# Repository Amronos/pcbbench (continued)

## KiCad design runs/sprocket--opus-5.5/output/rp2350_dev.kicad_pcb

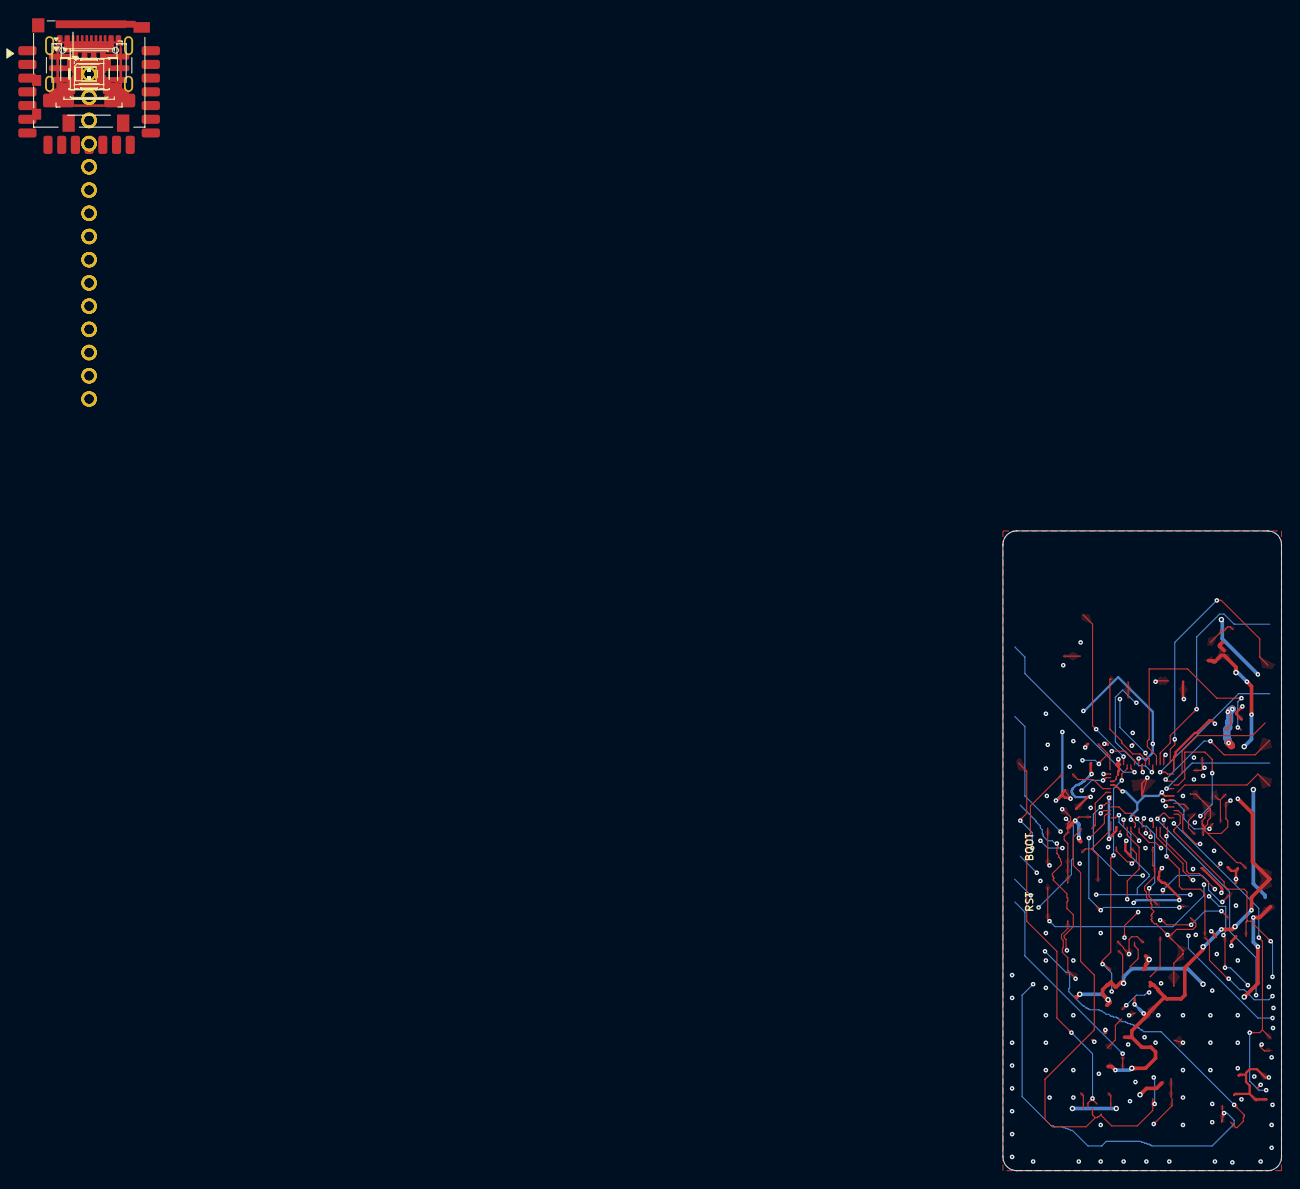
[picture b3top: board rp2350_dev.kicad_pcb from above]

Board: 4 copper layers, 30.5 x 70.0 mm, 82 parts (0 on the bottom side), 66 nets.

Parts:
C1: 4.7 µF; C_0603_1608Metric
C2, C3, C4, C5, C18, C30, C40: 10 µF; C_0603_1608Metric
C6, C7, C10, C11, C12, C13, C14, C15, C16, C17, C19, C20, C21, C27, C28, C31, C32, C41, C42: 100 nF; C_0402_1005Metric
C22, C23, C24, C29: 4.7 µF; C_0402_1005Metric
C25, C26: 15 pF; C_0402_1005Metric
D1: WS2812C-2020-V6; LED_WS2812B-2020_PLCC4_2.0x2.0mm
D2: red; LED_0603_1608Metric
FID1, FID2, FID3: Fiducial; Fiducial_1mm_Mask2mm
J1: USB-C; USB_C_Receptacle_GCT_USB4105-xx-A_16P_TopMnt_Horizontal
J2: microSD; microSD_HC_Molex_104031-0811
J3: Qwiic; JST_SH_SM04B-SRSS-TB_1x04-1MP_P1.00mm_Horizontal
J4: LiPo; JST_PH_S2B-PH-SM4-TB_1x02-1MP_P2.00mm_Horizontal
J5: Header L; PinHeader_1x15_P2.54mm_Vertical
J6: Header R; PinHeader_1x15_P2.54mm_Vertical
L1: 3.3 µH; L_Abracon_AOTA-B201610S
R1, R2: 5.1 kΩ; R_0402_1005Metric
R3, R31, R40, R41, R42, R43, R44, R45: 10 kΩ; R_0402_1005Metric
R4, R24: 2.7 kΩ; R_0402_1005Metric
R5: 1.6 kΩ; R_0402_1005Metric
R6, R21, R25: 1 kΩ; R_0402_1005Metric
R9, R10, R11, R13: 100 kΩ; R_0402_1005Metric
R12: 68 kΩ; R_0402_1005Metric
R20: 33 Ω; R_0402_1005Metric
R22, R23: 27 Ω; R_0402_1005Metric
R30: 470 Ω; R_0402_1005Metric
R46, R47: 4.7 kΩ; R_0402_1005Metric
SW1: BOOTSEL; SW_SPST_PTS810
SW2: RESET; SW_SPST_PTS810
U1: RP2350A; QFN-60-1EP_7x7mm_P0.4mm_EP3.4x3.4mm
U2: W25Q128JVSIQ; SOIC-8_5.3x5.3mm_P1.27mm
U3: APS6404L-3SQR-SN; SOIC-8_3.9x4.9mm_P1.27mm
U4: RMC20452T
U5: BQ24074RGTR; VQFN-16-1EP_3x3mm_P0.5mm_EP1.68x1.68mm_ThermalVias
U6: TLV75733PDBVR; SOT-23-5
U7: USBLC6-2SC6; SOT-23-6
Y1: 12 MHz; Crystal_SMD_3225-4Pin_3.2x2.5mm

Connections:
3V3_EN: J5.14, R9.2, U6.3 (EN)
+1V1: C19.1, C20.1, C21.1, C23.1, C29.1, L1.2, U1.6 (DVDD), U1.23 (DVDD), U1.39 (DVDD), U1.50 (VREG_FB)
+3V3: C5.1, C6.1, C10.1, C11.1, C12.1, C13.1, C14.1, C15.1, C16.1, C17.1, C18.1, C22.1, C27.1, C28.1, C32.1, C40.1, C41.1, C42.1, D1.4 (VDD), J2.4 (VDD), J3.2, J5.4, J6.11, R20.1, R24.1, R40.1, R41.1, R42.1, R43.1, R44.1, R45.1, R46.1, R47.1, U1.1 (IOVDD), U1.11 (IOVDD), U1.20 (IOVDD), U1.30 (IOVDD), U1.38 (IOVDD), U1.44 (ADC_AVDD), U1.45 (IOVDD), U1.49 (VREG_VIN), U1.53 (USB_OTP_VDD), U1.54 (QSPI_IOVDD), U2.8 (VCC), U3.8 (VDD), U4.14 (VDDIO), U6.5 (OUT)
/mcu/BOOT_SW: R25.2, SW1.1
/mcu/PSRAM_CS: R24.2, U1.12 (GPIO8), U3.1 (~CE)
/mcu/QSPI_SCLK: U1.56 (QSPI_SCLK), U2.6 (CLK), U3.6 (SCLK)
/mcu/QSPI_SD0: U1.57 (QSPI_SD0), U2.5 (DI/IO_{0}), U3.5 (SI/SIO0)
/mcu/QSPI_SD1: U1.59 (QSPI_SD1), U2.2 (DO/IO_{1}), U3.2 (SO/SIO1)
/mcu/QSPI_SD2: U1.58 (QSPI_SD2), U2.3 (~WP/IO_{2}), U3.3 (SIO2)
/mcu/QSPI_SD3: U1.55 (QSPI_SD3), U2.7 (~HOLD/~RESET/IO_{3}), U3.7 (SIO3)
/mcu/QSPI_SS: R25.1, U1.60 (~QSPI_SS), U2.1 (~CS)
/mcu/USB_DM_MCU: R23.2, U1.51 (USB_DM)
/mcu/USB_DP_MCU: R22.2, U1.52 (USB_DP)
/mcu/VREG_AVDD: C24.1, R20.2, U1.46 (VREG_AVDD)
/mcu/VREG_LX: L1.1, U1.48 (VREG_LX)
/mcu/XIN: C25.1, U1.21 (XIN), Y1.1
/mcu/XOUT: R21.2, U1.22 (XOUT)
/mcu/XTAL_O: C26.1, R21.1, Y1.3
/power/BQ_ILIM: R5.1, U5.12 (ILIM)
/power/BQ_ISET: R4.1, U5.16 (ISET)
/power/BQ_TS: R3.1, U5.1 (TS)
/power/CC1: J1.A5 (CC1), R1.1
/power/CC2: J1.B5 (CC2), R2.1
/power/CHG_LED_K: D2.1 (K), R6.1
/power/CHG_N: R6.2, U5.9 (~CHG)
/wireless/WL_DOUT: R30.2, U4.6 (WL_DATA_OUT)
/wireless/WL_IRQ: R31.2, U4.10 (~WL_IRQ)
GND: C1.2, C2.2, C3.2, C4.2, C5.2, C6.2, C7.2, C10.2, C11.2, C12.2, C13.2, C14.2, C15.2, C16.2, C17.2, C18.2, C19.2, C20.2, C21.2, C22.2, C23.2, C24.2, C25.2, C26.2, C27.2, C28.2, C29.2, C30.2, C31.2, C32.2, C40.2, C41.2, C42.2, D1.2 (VSS), J1.A1 (GND), J1.A12 (GND), J1.B1 (GND), J1.B12 (GND), J1.SH (SHIELD), J2.6 (VSS), J2.10 (DET_A), J2.SH (SHIELD), J3.1, J4.1, J5.1, J5.5, J5.15, J6.1, J6.15, R1.2, R2.2, R3.2, R4.2, R5.2, R11.2, R13.2, SW1.2, SW2.2, U1.47 (VREG_PGND), U1.61 (GND), U2.4 (GND), U3.4 (VSS), U4.1 (GND), U4.4 (GND), U4.7 (GND), U4.11 (GND), U4.15 (GND), U4.21 (GND), U5.4 (~CE), U5.5 (EN2), U5.8 (VSS), U5.17 (VSS), U6.2 (GND), U7.2 (GND), Y1.2 (G), Y1.4 (G)
GPIO0: J5.6, U1.2 (GPIO0)
GPIO1: J5.7, U1.3 (GPIO1)
GPIO2: J5.8, U1.4 (GPIO2)
GPIO3: J5.9, U1.5 (GPIO3)
GPIO6: J5.12, U1.9 (GPIO6)
GPIO7: J5.13, U1.10 (GPIO7)
GPIO16: J6.7, U1.27 (GPIO16)
GPIO17: J6.6, U1.28 (GPIO17)
GPIO18: J6.5, U1.29 (GPIO18)
GPIO19: J6.4, U1.31 (GPIO19)
GPIO20: J6.3, U1.32 (GPIO20)
GPIO21: J6.2, U1.33 (GPIO21)
GPIO26: J5.2, U1.40 (GPIO26/ADC0)
GPIO27: J5.3, U1.41 (GPIO27/ADC1)
I2C_SCL: J3.4, J5.11, R47.2, U1.8 (GPIO5)
I2C_SDA: J3.3, J5.10, R46.2, U1.7 (GPIO4)
LED_DIN: D1.3 (DIN), U1.34 (GPIO22)
RUN: J6.10, SW2.1, U1.26 (RUN)
SD_CLK: J2.5 (CLK), U1.14 (GPIO10)
SD_CMD: J2.3 (CMD), R42.2, U1.15 (GPIO11)
SD_D0: J2.7 (DAT0), R43.2, U1.16 (GPIO12)
SD_D1: J2.8 (DAT1), R44.2, U1.17 (GPIO13)
SD_D2: J2.1 (DAT2), R40.2, U1.18 (GPIO14)
SD_D3: J2.2 (DAT3/CD), R41.2, U1.19 (GPIO15)
SD_DET: J2.9 (DET_B), R45.2, U1.13 (GPIO9)
SWCLK: J6.9, U1.24 (SWCLK)
SWDIO: J6.8, U1.25 (SWDIO)
USB_DM: J1.A7 (D-), J1.B7 (D-), R23.1, U7.3 (I/O2), U7.4 (I/O2)
USB_DP: J1.A6 (D+), J1.B6 (D+), R22.1, U7.1 (I/O1), U7.6 (I/O1)
VBAT: C3.1, J4.2, J6.12, R10.1, U5.2 (BAT), U5.3 (BAT)
VBAT_SENSE: C7.1, R10.2, R11.1, U1.42 (GPIO28/ADC2)
VBUS: C1.1, D2.2 (A), J1.A4 (VBUS), J1.A9 (VBUS), J1.B4 (VBUS), J1.B9 (VBUS), J6.14, R12.1, U5.13 (IN), U7.5 (VBUS)
VBUS_SENSE: R12.2, R13.1, U4.17 (WL_GPIO2)
VSYS: C2.1, C4.1, C30.1, C31.1, J6.13, R9.1, U4.16 (VIN), U5.6 (EN1), U5.10 (OUT), U5.11 (OUT), U6.1 (IN)
WL_CLK: U1.43 (GPIO29/ADC3), U4.3 (WL_CLK)
WL_CS: U1.37 (GPIO25), U4.9 (WL_CS)
WL_D: R30.1, R31.1, U1.36 (GPIO24), U4.5 (WL_DATA_IN)
WL_ON: U1.35 (GPIO23), U4.12 (WL_ON), U4.13 (BT_ON)

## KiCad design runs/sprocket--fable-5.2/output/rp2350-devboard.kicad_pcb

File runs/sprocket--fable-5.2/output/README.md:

# RP2350 Wi-Fi dev board

A 76.2 × 25.4 mm, 4-layer RP2350A board laid out for PCBWay turnkey assembly. All assembled parts sit on the top side. The two 1×12 headers are fitted on the bottom, 22.86 mm (0.9 in) apart, so the board plugs into a breadboard with one free hole per side.

| Block | Part | Notes |
|---|---|---|
| MCU | RP2350A (SC1509-A4), QFN-60 | Order the A4 stepping. Core regulator copies Raspberry Pi's reference layout. |
| Flash | W25Q128JVPIQ, 16 MB, WSON-8 | QSPI CS0. IQ variant has QE fixed to 1. |
| PSRAM | APS6404L-3SQR-SN, 8 MB, SOP-8 | QSPI CS1 on GPIO8, 2.2 kΩ pull-up R19 |
| Crystal | ABM8-272-T3 12 MHz | 15 pF load caps, 1 kΩ series on XOUT, as on Pico 2 |
| USB | GCT USB4105-GF-A USB-C, USBLC6-2SC6 ESD, 27 Ω series | USB 2.0 full speed. 5.1 kΩ Rd on each CC pin. |
| Charger | BQ24074RGTR with power path | USB500 mode: 500 mA input limit, 494 mA charge (R6 1.8 kΩ), 10 kΩ TS resistor in place of a thermistor |
| 3.3 V | TLV75733PDBVR LDO, 1 A | Input is VSYS. EN is pulled up to VSYS and brought out to J7. |
| Battery | JST PH 2-pin (S2B-PH-SM4-TB) | Pin 1 is +, marked on silkscreen. VBAT/2 on GPIO28 (ADC2). |
| Radio | Raspberry Pi RM2 (CYW43439), Wi-Fi 4 + BLE 5.2 | Same GPIO23/24/25/29 wiring as Pico 2 W |
| microSD | Hirose DM3AT-SF-PEJM5 | GPIO10 to GPIO15, usable as SPI1 or 4-bit SDIO via PIO. 10 kΩ pull-ups, 10 µF local bulk. |
| Qwiic | JST SH 4-pin | I2C0 on GPIO4/GPIO5, 2.2 kΩ pull-ups |
| Debug | JST SH 3-pin | Raspberry Pi debug connector pinout, 100 Ω series |
| RGB LED | WS2812B-2020-V6 on GPIO9 | V6 is the variant rated for 3.3 V supply |
| LEDs | Green = power good, amber = charging, green = user LED on RM2 WL_GPIO0 | |
| Buttons | BOOT (QSPI_SS via 1 kΩ), RST (RUN) | |

## Pinout

Viewed from the top with the USB-C connector on the left, J6 is the top edge and J7 the bottom edge. Pin 1 of each header is next to the USB end. The same labels are printed on the bottom silkscreen.

| Pin | J6 (top edge) | J7 (bottom edge) |
|---|---|---|
| 1 | VBUS (5 V, straight from USB-C) | 3V3 |
| 2 | VSYS (charger output, 3.5 to 4.4 V) | EN (LDO enable, pull low to turn 3V3 off) |
| 3 | GND | RUN (low = reset) |
| 4 | GP27 / A1 | GND |
| 5 | GP26 / A0 | GP0 |
| 6 | GP22 | GP1 |
| 7 | GP21 | GP2 |
| 8 | GP20 | GP3 |
| 9 | GP19 | GP4 / SDA (shared with Qwiic) |
| 10 | GP18 | GP5 / SCL (shared with Qwiic) |
| 11 | GP17 | GP6 |
| 12 | GP16 | GP7 |

Internal GPIOs:

| GPIO | Use |
|---|---|
| 8 | PSRAM chip select (XIP_CS1n) |
| 9 | WS2812B data |
| 10 / 11 | microSD CLK / CMD |
| 12 to 15 | microSD DAT0 to DAT3 (DAT3 is CS in SPI mode) |
| 23 / 24 / 25 / 29 | RM2 WL_ON / data / CS / clock, as on Pico 2 W |
| 28 | Battery voltage / 2 (ADC2) |

## Firmware notes

- Start from pico-sdk's `pico2_w` board file and change `PICO_FLASH_SIZE_BYTES` to 16 MB. Remove its VSYS sense on GPIO29 and VBUS sense on WL_GPIO2. RM2 GPIO1 and GPIO2 are not connected here.
- Battery voltage is `2 × ADC2`. Call `adc_gpio_init(28)` so the digital input is off.
- Disable the GPIO8 pad pull-down before enabling XIP_CS1 for the PSRAM.
- The microSD card-detect switch is not connected. Firmware has to probe for a card.
- There is no GPIO for USB presence or charger status. The LEDs show PGOOD and CHG only.

## Layout decisions

- Stackup is PCBWay's standard 4-layer 1.6 mm with 1 oz copper on all layers: F.Cu signals with GND fill, In1 solid GND, In2 3V3 plane with a few signal tracks, B.Cu signals with GND fill. The stackup is written into the board file (7628 prepreg 0.1855 mm, core 1.03 mm, ENIG).
- Rules follow the strictest values in [`scratch/pcbway-notes.md`](scratch/pcbway-notes.md): 0.127 mm (5 mil) track and gap, 0.25 mm drill / 0.55 mm via, 0.15 mm annular ring, 0.5 mm hole to hole, 0.3 mm copper to edge. Two local exceptions are in `rp2350-devboard.kicad_dru`: 0.13 mm around VREG_LX, where the reference layout runs it between 0402 pads, and the USB4105's own peg-to-pad spacing.
- The core regulator (L1, C6, C7, C8) copies Raspberry Pi's reference layout, as the RP2350 datasheet requires. The QSPI bus, U1 fan-out and USB pair were routed by script and locked. An autorouter finished the rest.
- The USB pair is 0.22 mm / 0.15 mm gap over the In1 ground plane. It is not impedance controlled, which full speed USB does not need.
- Power tracks: VBUS and VSYS 0.5 mm, +BATT and 3V3 0.3 mm. 3V3 also uses the In2 plane.
- 40 GND return vias next to signal layer changes, 21 GND stitching vias, and teardrops on all pads and vias.
- The last 5 mm under the RM2 antenna is a keep-out with no copper on any layer. Keep metal away from that end in an enclosure.
- Three fiducials are on the top side. There are no mounting holes: the board is held by its headers.

## Caveats

These come from the design reviews in `scratch/review-*.md` and were accepted, not fixed:

- 3V3 back-feed: anything that powers J7.1 or the Qwiic 3V3 pin while the board is off drives the LDO output above its input. Do not feed 3V3 from outside.
- VBUS on J6.1 is tied straight to USB-C. 5 V fed there back-feeds a connected host. It is not 28 V tolerant, because U6 breaks down at 6 V.
- Battery drain: the 100 kΩ / 100 kΩ divider draws about 21 µA from the cell all the time. With 3V3 off it also feeds GPIO28 through 100 kΩ, which is current-limited and was judged safe.
- No battery protection on the board. Use a cell with its own protection circuit, 500 mAh or larger so 494 mA stays under 1C. Check polarity of third-party cells: many have red and black swapped.
- Without a battery the 500 mA USB limit covers RP2350, Wi-Fi transmit, SD writes and the RGB LED. Heavy peaks can brown out the 3V3 rail. A battery supplements the input.
- On battery, 3V3 drops out of regulation below about 3.5 V. Firmware should stop Wi-Fi and SD writes near 3.4 V.
- GP26 to GP29 are not 5 V tolerant. The other header GPIOs tolerate 5 V only while 3V3 is on.
- No ESD protection on Qwiic, debug or microSD lines.

### Not verified

- DM3AT card-detect pin numbering against the Hirose drawing. The pins are unused, so a mismatch only matters for a later revision.
- PTS810 pad pairing. The KiCad footprint assumes pads 1 and 2 are the switched pair.
- L1 orientation: the AOTA inductor is polarised, and the dot must go to pad 1 (+1V1). This was checked against the footprint, not a physical part.
- No board has been built or measured. All checks are ERC, DRC and datasheet reviews.

## Library notes

- `lib_footprint_mismatch` is set to ignore in the project. J5, J6, J7 and U7 differ from their library copies on purpose: their silkscreen was trimmed where it crossed the board edge.
- KiCad has no 3D models for J2 and D1. Their STEP files in `lib/3d/` came from LCSC through easyeda2kicad (C295747 and C965555, the same 2020 package as the V6 part). The J2 model offset of (1, -3, 0) mm was fitted by eye from renders. These models only affect the renders.
- RM2 symbol and footprint live in `lib/` and match Raspberry Pi's own KiCad footprint.

## Ordering from PCBWay

Upload `fab/rp2350-devboard-gerbers.zip`, `fab/bom-pcbway.csv` and `fab/centroid-top.csv`.

| Setting | Value |
|---|---|
| Layers | 4, order F.Cu / In1.Cu / In2.Cu / B.Cu |
| Thickness | 1.6 mm, standard stackup |
| Min track / spacing | 5/5 mil |
| Min hole | 0.25 mm |
| Copper | 1 oz outer, 1 oz inner |
| Solder mask / silkscreen | Green / white |
| Surface finish | ENIG |
| Panel | Panel by supplier with break-away rails on the long edges. The board is under 50 mm wide and USB-C is at the edge. |
| Assembly | Turnkey, top side only. J6 and J7 are through-hole on the bottom, see BOM notes. |
| Substitutes | No, except lines marked "Yes" in the BOM's substitutes column |
| X-ray | Ask for it on U1 (QFN-60) and U7 (RM2, LGA pads). The price is not in the instant quote. |

Text for the order notes field:

> Machine placement and reflow please, no hand soldering of U1. J1 shell legs are plated through-hole: pin-in-paste or hand solder. J6 and J7 are 1x12 headers fitted on the bottom side, pins pointing down, soldered from the top. L1 is polarised: dot to pad 1, marked on silkscreen. Please quote X-ray for U1 and U7.

Questions for the sales rep are listed at the end of `scratch/pcbway-notes.md`.

## Files

| Path | Content |
|---|---|
| `rp2350-devboard.kicad_pro` / `.kicad_sch` / `.kicad_pcb` | KiCad project |
| `lib/` | RM2 symbol and footprint, J2 and D1 STEP models |
| `docs/schematic.pdf`, `docs/rp2350-devboard.png` | Schematic exports |
| `fab/gerbers/` | 11 Gerber layers, PTH and NPTH drill files, drill maps, Gerber job file |
| `fab/rp2350-devboard-gerbers.zip` | The same files zipped for upload |
| `fab/bom-pcbway.csv` | PCBWay BOM with MPN, LCSC, Digi-Key and Mouser numbers, notes and substitutes |
| `fab/centroid-top.csv` | Pick and place, mm from the bottom-left corner (drill origin) |
| `fab/assembly-top.pdf`, `fab/assembly-bottom.pdf` | Assembly drawings |
| `fab/render-*.png` | 3D renders |
| `scratch/pcbway-notes.md` | PCBWay capabilities with sources, used to set the rules |
| `scratch/review-*.md`, `scratch/jst-polarity.md` | Design reviews |
| `scratch/sch/`, `scratch/pcb/`, `scratch/route/` | Scripts that generate the schematic, place, route and export the board |

### Regenerating

1. `bash scratch/sch/gen_real.sh` rebuilds the schematic, runs ERC and writes the netlist.
2. `scratch/pcb/02_place.py` places parts from `place.json`. `05_fanout.py` draws the hand-routed blocks and the U1 fan-out.
3. `IN2COST=6 bash scratch/route/full.sh g` routes the rest. Copy `g_best.kicad_pcb` to the root.
4. Run `06_unused_vias.py`, then the GND via pass: `route_planes.py rp2350-devboard.kicad_pcb --nets GND GND GND --plane-layers F.Cu In1.Cu B.Cu --skip-existing-zones --no-thermal-vias --stitch-vias --stitch-pitch 4 --add-gnd-vias --hole-to-hole-clearance 0.55`. Then `07_teardrops.py`, `08_silk.py`, and `09_fab.py`, which writes `fab/`.
5. `bash scratch/pcb/drc.sh` runs DRC with schematic parity.

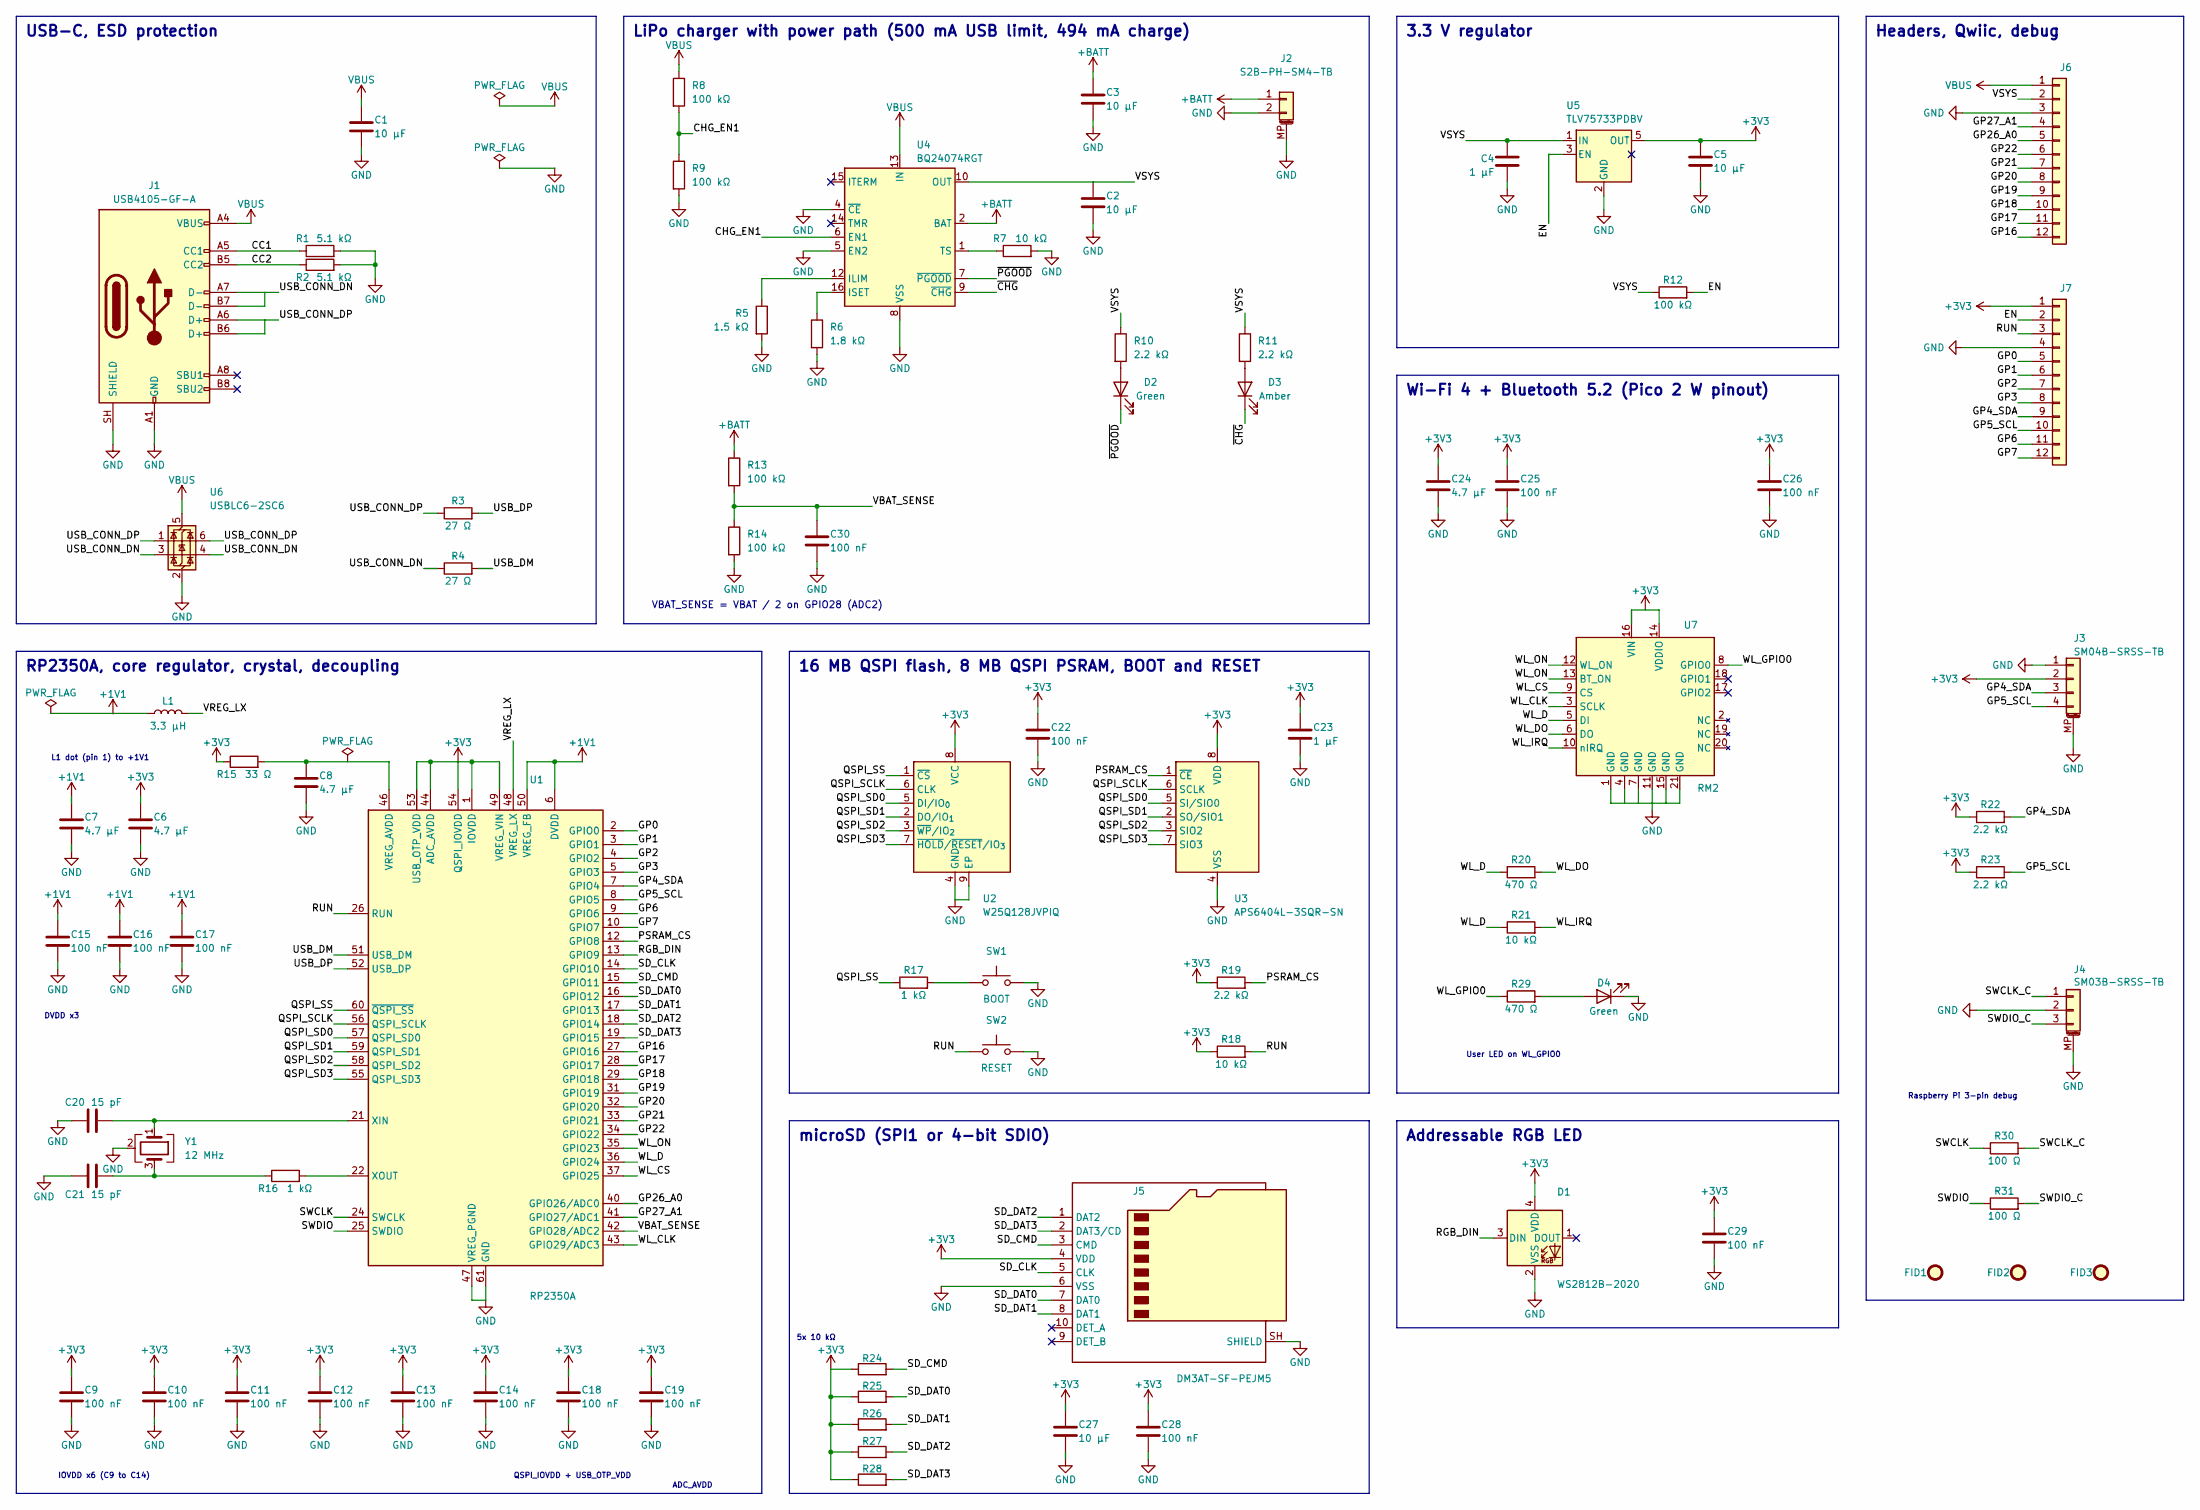
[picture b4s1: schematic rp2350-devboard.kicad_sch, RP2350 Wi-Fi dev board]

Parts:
C1, C2, C3, C5: 10 µF; C_0603_1608Metric; MPN GRM188R61E106MA73D; Digikey Part # 490-7202-1-ND
C4, C23: 1 µF; C_0402_1005Metric; MPN GRM155R61C105KA12D; Digikey Part # 490-10694-1-ND
C6, C7, C8, C24: 4.7 µF; C_0402_1005Metric; MPN GRM155R60J475ME47D; Digikey Part # 490-5915-1-ND
C9, C10, C11, C12, C13, C14, C15, C16, C17, C18, C19, C22, C25, C26, C28, C29, C30: 100 nF; C_0402_1005Metric; MPN GRM155R71C104KA88D; Digikey Part # 490-3261-1-ND
C20, C21: 15 pF; C_0402_1005Metric; MPN GRM1555C1H150JA01D; Digikey Part # 490-5888-1-ND
C27: 10 µF; C_0402_1005Metric; MPN GRM155R60J106ME15D; Digikey Part # 490-13238-1-ND
D1: WS2812B-2020; LED_WS2812B-2020_PLCC4_2.0x2.0mm; MPN WS2812B-2020-V6; LCSC Part # C52917434
D2, D4: Green; LED_0603_1608Metric; MPN 150060GS75000; Digikey Part # 732-4971-1-ND
D3: Amber; LED_0603_1608Metric; MPN 150060AS75000; Digikey Part # 732-150060AS75000CT-ND
FID1, FID2, FID3: Fiducial; Fiducial_1mm_Mask2mm
J1: USB4105-GF-A; USB_C_Receptacle_GCT_USB4105-xx-A_16P_TopMnt_Horizontal; MPN USB4105-GF-A; Digikey Part # 2073-USB4105-GF-ACT-ND
J2: S2B-PH-SM4-TB; JST_PH_S2B-PH-SM4-TB_1x02-1MP_P2.00mm_Horizontal; MPN S2B-PH-SM4-TB; Digikey Part # 455-S2B-PH-SM4-TBCT-ND
J3: SM04B-SRSS-TB; JST_SH_SM04B-SRSS-TB_1x04-1MP_P1.00mm_Horizontal; MPN SM04B-SRSS-TB; Digikey Part # 455-SM04B-SRSS-TBCT-ND
J4: SM03B-SRSS-TB; JST_SH_SM03B-SRSS-TB_1x03-1MP_P1.00mm_Horizontal; MPN SM03B-SRSS-TB; Digikey Part # 455-SM03B-SRSS-TBCT-ND
J5: DM3AT-SF-PEJM5; microSD_HC_Hirose_DM3AT-SF-PEJM5; MPN DM3AT-SF-PEJM5; Digikey Part # HR1964CT-ND
J6, J7: 1x12 2.54 mm; PinHeader_1x12_P2.54mm_Vertical; MPN 61301211121; Digikey Part # 732-5323-ND
L1: 3.3 µH; L_Abracon_AOTA-B201610S; MPN AOTA-B201610S3R3-101-T; Digikey Part # 535-AOTA-B201610S3R3-101-TCT-ND
R1, R2: 5.1 kΩ; R_0402_1005Metric; MPN RC0402FR-075K1L; Digikey Part # 311-5.10KLRCT-ND
R3, R4: 27 Ω; R_0402_1005Metric; MPN RC0402FR-0727RL; Digikey Part # YAG3086CT-ND
R5: 1.5 kΩ; R_0402_1005Metric; MPN RC0402FR-071K5L; Digikey Part # 311-1.50KLRCT-ND
R6: 1.8 kΩ; R_0402_1005Metric; MPN RC0402FR-071K8L; Digikey Part # 311-1.80KLRCT-ND
R7, R18, R21, R24, R25, R26, R27, R28: 10 kΩ; R_0402_1005Metric; MPN RC0402FR-0710KL; Digikey Part # 311-10.0KLRCT-ND
R8, R9, R12, R13, R14: 100 kΩ; R_0402_1005Metric; MPN RC0402FR-07100KL; Digikey Part # 311-100KLRCT-ND
R10, R11, R19, R22, R23: 2.2 kΩ; R_0402_1005Metric; MPN RC0402FR-072K2L; Digikey Part # 311-2.20KLRCT-ND
R15: 33 Ω; R_0402_1005Metric; MPN RC0402FR-0733RL; Digikey Part # 311-33.0LRCT-ND
R16, R17: 1 kΩ; R_0402_1005Metric; MPN RC0402FR-071KL; Digikey Part # 311-1.00KLRCT-ND
R20, R29: 470 Ω; R_0402_1005Metric; MPN RC0402FR-07470RL; Digikey Part # 311-470LRCT-ND
R30, R31: 100 Ω; R_0402_1005Metric; MPN RC0402FR-07100RL; Digikey Part # 311-100LRCT-ND
SW1: BOOT; SW_SPST_PTS810; MPN PTS810 SJM 250 SMTR LFS; Digikey Part # CKN10502CT-ND
SW2: RESET; SW_SPST_PTS810; MPN PTS810 SJM 250 SMTR LFS; Digikey Part # CKN10502CT-ND
U1: RP2350A; QFN-60-1EP_7x7mm_P0.4mm_EP3.4x3.4mm; MPN SC1509-A4; Digikey Part # 2648-SC1509-A4CT-ND
U2: W25Q128JVPIQ; WSON-8-1EP_6x5mm_P1.27mm_EP3.4x4.3mm; MPN W25Q128JVPIQ; Digikey Part # 256-W25Q128JVPIQ-TUBE-ND
U3: APS6404L-3SQR-SN; SOIC-8_3.9x4.9mm_P1.27mm; MPN APS6404L-3SQR-SN; Mouser Part # 878-APS6404L-3SQR-SN
U4: BQ24074RGT; VQFN-16-1EP_3x3mm_P0.5mm_EP1.6x1.6mm; MPN BQ24074RGTR; Digikey Part # 296-38873-1-ND
U5: TLV75733PDBV; SOT-23-5; MPN TLV75733PDBVR; Digikey Part # 296-50414-1-ND
U6: USBLC6-2SC6; SOT-23-6; MPN USBLC6-2SC6; Digikey Part # 497-5235-1-ND
U7: RM2; RaspberryPi_RM2; MPN SC1169; Digikey Part # 2648-SC1169CT-ND
Y1: 12 MHz; Crystal_SMD_3225-4Pin_3.2x2.5mm; MPN ABM8-272-T3; Digikey Part # 535-ABM8-272-T3CT-ND

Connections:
+1V1: C7.1, C15.1, C16.1, C17.1, L1.1, U1.6 (DVDD), U1.23 (DVDD), U1.39 (DVDD), U1.50 (VREG_FB)
+3V3: C5.1, C6.1, C9.1, C10.1, C11.1, C12.1, C13.1, C14.1, C18.1, C19.1, C22.1, C23.1, C24.1, C25.1, C26.1, C27.1, C28.1, C29.1, D1.4 (VDD), J3.2, J5.4 (VDD), J7.1, R15.1, R18.1, R19.1, R22.1, R23.1, R24.1, R25.1, R26.1, R27.1, R28.1, U1.1 (IOVDD), U1.11 (IOVDD), U1.20 (IOVDD), U1.30 (IOVDD), U1.38 (IOVDD), U1.44 (ADC_AVDD), U1.45 (IOVDD), U1.49 (VREG_VIN), U1.53 (USB_OTP_VDD), U1.54 (QSPI_IOVDD), U2.8 (VCC), U3.8 (VDD), U5.5 (OUT), U7.14 (VDDIO), U7.16 (VIN)
+BATT: C3.1, J2.1, R13.1, U4.2 (BAT), U4.3 (BAT)
/CC1: J1.A5 (CC1), R1.1
/CC2: J1.B5 (CC2), R2.1
/CHG_EN1: R8.2, R9.1, U4.6 (EN1)
/EN: J7.2, R12.2, U5.3 (EN)
/GP0: J7.5, U1.2 (GPIO0)
/GP1: J7.6, U1.3 (GPIO1)
/GP2: J7.7, U1.4 (GPIO2)
/GP3: J7.8, U1.5 (GPIO3)
/GP4_SDA: J3.3, J7.9, R22.2, U1.7 (GPIO4)
/GP5_SCL: J3.4, J7.10, R23.2, U1.8 (GPIO5)
/GP6: J7.11, U1.9 (GPIO6)
/GP7: J7.12, U1.10 (GPIO7)
/GP16: J6.12, U1.27 (GPIO16)
/GP17: J6.11, U1.28 (GPIO17)
/GP18: J6.10, U1.29 (GPIO18)
/GP19: J6.9, U1.31 (GPIO19)
/GP20: J6.8, U1.32 (GPIO20)
/GP21: J6.7, U1.33 (GPIO21)
/GP22: J6.6, U1.34 (GPIO22)
/GP26_A0: J6.5, U1.40 (GPIO26/ADC0)
/GP27_A1: J6.4, U1.41 (GPIO27/ADC1)
/PSRAM_CS: R19.2, U1.12 (GPIO8), U3.1 (~CE)
/QSPI_SCLK: U1.56 (QSPI_SCLK), U2.6 (CLK), U3.6 (SCLK)
/QSPI_SD0: U1.57 (QSPI_SD0), U2.5 (DI/IO_{0}), U3.5 (SI/SIO0)
/QSPI_SD1: U1.59 (QSPI_SD1), U2.2 (DO/IO_{1}), U3.2 (SO/SIO1)
/QSPI_SD2: U1.58 (QSPI_SD2), U2.3 (~WP/IO_{2}), U3.3 (SIO2)
/QSPI_SD3: U1.55 (QSPI_SD3), U2.7 (~HOLD/~RESET/IO_{3}), U3.7 (SIO3)
/QSPI_SS: R17.1, U1.60 (~QSPI_SS), U2.1 (~CS)
/RGB_DIN: D1.3 (DIN), U1.13 (GPIO9)
/RUN: J7.3, R18.2, SW2.1, U1.26 (RUN)
/SD_CLK: J5.5 (CLK), U1.14 (GPIO10)
/SD_CMD: J5.3 (CMD), R24.2, U1.15 (GPIO11)
/SD_DAT0: J5.7 (DAT0), R25.2, U1.16 (GPIO12)
/SD_DAT1: J5.8 (DAT1), R26.2, U1.17 (GPIO13)
/SD_DAT2: J5.1 (DAT2), R27.2, U1.18 (GPIO14)
/SD_DAT3: J5.2 (DAT3/CD), R28.2, U1.19 (GPIO15)
/SWCLK: R30.1, U1.24 (SWCLK)
/SWCLK_C: J4.1, R30.2
/SWDIO: R31.1, U1.25 (SWDIO)
/SWDIO_C: J4.3, R31.2
/USB_CONN_DN: J1.A7 (D-), J1.B7 (D-), R4.1, U6.3 (I/O2), U6.4 (I/O2)
/USB_CONN_DP: J1.A6 (D+), J1.B6 (D+), R3.1, U6.1 (I/O1), U6.6 (I/O1)
/USB_DM: R4.2, U1.51 (USB_DM)
/USB_DP: R3.2, U1.52 (USB_DP)
/VBAT_SENSE: C30.1, R13.2, R14.1, U1.42 (GPIO28/ADC2)
/VREG_LX: L1.2, U1.48 (VREG_LX)
/VSYS: C2.1, C4.1, J6.2, R10.1, R11.1, R12.1, U4.10 (OUT), U4.11 (OUT), U5.1 (IN)
/WL_CLK: U1.43 (GPIO29/ADC3), U7.3 (SCLK)
/WL_CS: U1.37 (GPIO25), U7.9 (CS)
/WL_D: R20.1, R21.1, U1.36 (GPIO24), U7.5 (DI)
/WL_DO: R20.2, U7.6 (DO)
/WL_GPIO0: R29.1, U7.8 (GPIO0)
/WL_IRQ: R21.2, U7.10 (nIRQ)
/WL_ON: U1.35 (GPIO23), U7.12 (WL_ON), U7.13 (BT_ON)
/~CHG: D3.1 (K), U4.9 (~CHG)
/~PGOOD: D2.1 (K), U4.7 (~PGOOD)
GND: C1.2, C2.2, C3.2, C4.2, C5.2, C6.2, C7.2, C8.2, C9.2, C10.2, C11.2, C12.2, C13.2, C14.2, C15.2, C16.2, C17.2, C18.2, C19.2, C20.1, C21.1, C22.2, C23.2, C24.2, C25.2, C26.2, C27.2, C28.2, C29.2, C30.2, D1.2 (VSS), D4.1 (K), J1.A1 (GND), J1.A12 (GND), J1.B1 (GND), J1.B12 (GND), J1.SH (SHIELD), J2.2, J2.MP (MountPin), J3.1, J3.MP (MountPin), J4.2, J4.MP (MountPin), J5.6 (VSS), J5.SH (SHIELD), J6.3, J7.4, R1.2, R2.2, R5.2, R6.2, R7.2, R9.2, R14.2, SW1.2, SW2.2, U1.47 (VREG_PGND), U1.61 (GND), U2.4 (GND), U2.9 (EP), U3.4 (VSS), U4.4 (~CE), U4.5 (EN2), U4.8 (VSS), U4.17 (VSS), U5.2 (GND), U6.2 (GND), U7.1 (GND), U7.4 (GND), U7.7 (GND), U7.11 (GND), U7.15 (GND), U7.21 (GND), Y1.2 (G), Y1.4 (G)
unnamed: C21.2, R16.1, Y1.3
unnamed: D2.2 (A), R10.2
unnamed: D3.2 (A), R11.2
unnamed: D4.2 (A), R29.2
unnamed: R17.2, SW1.1
unnamed: C8.1, R15.2, U1.46 (VREG_AVDD)
unnamed: C20.2, U1.21 (XIN), Y1.1
unnamed: R16.2, U1.22 (XOUT)
unnamed: R5.1, U4.12 (ILIM)
unnamed: R6.1, U4.16 (ISET)
unnamed: R7.1, U4.1 (TS)
VBUS: C1.1, J1.A4 (VBUS), J1.A9 (VBUS), J1.B4 (VBUS), J1.B9 (VBUS), J6.1, R8.1, U4.13 (IN), U6.5 (VBUS)

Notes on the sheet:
DVDD x3
3.3 V regulator
ADC_AVDD
Raspberry Pi 3-pin debug
L1 dot (pin 1) to +1V1
16 MB QSPI flash, 8 MB QSPI PSRAM, BOOT and RESET
Wi-Fi 4 + Bluetooth 5.2 (Pico 2 W pinout)
5x 10 kΩ
VBAT_SENSE = VBAT / 2 on GPIO28 (ADC2)
Headers, Qwiic, debug
microSD (SPI1 or 4-bit SDIO)
QSPI_IOVDD + USB_OTP_VDD
USB-C, ESD protection
User LED on WL_GPIO0
LiPo charger with power path (500 mA USB limit, 494 mA charge)
RP2350A, core regulator, crystal, decoupling
IOVDD x6 (C9 to C14)
Addressable RGB LED

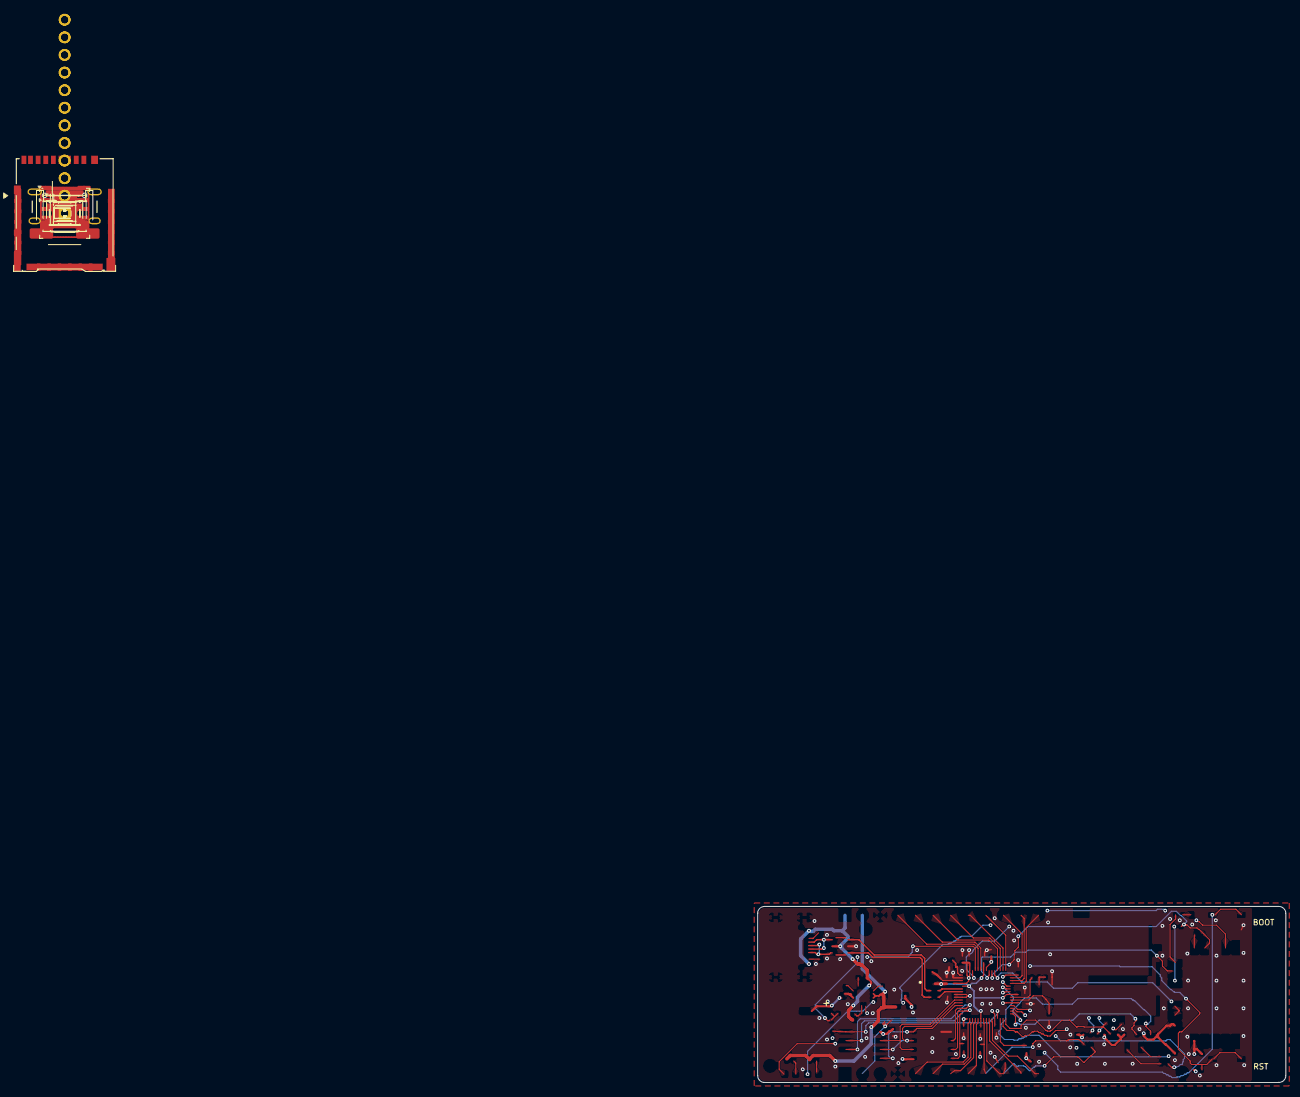
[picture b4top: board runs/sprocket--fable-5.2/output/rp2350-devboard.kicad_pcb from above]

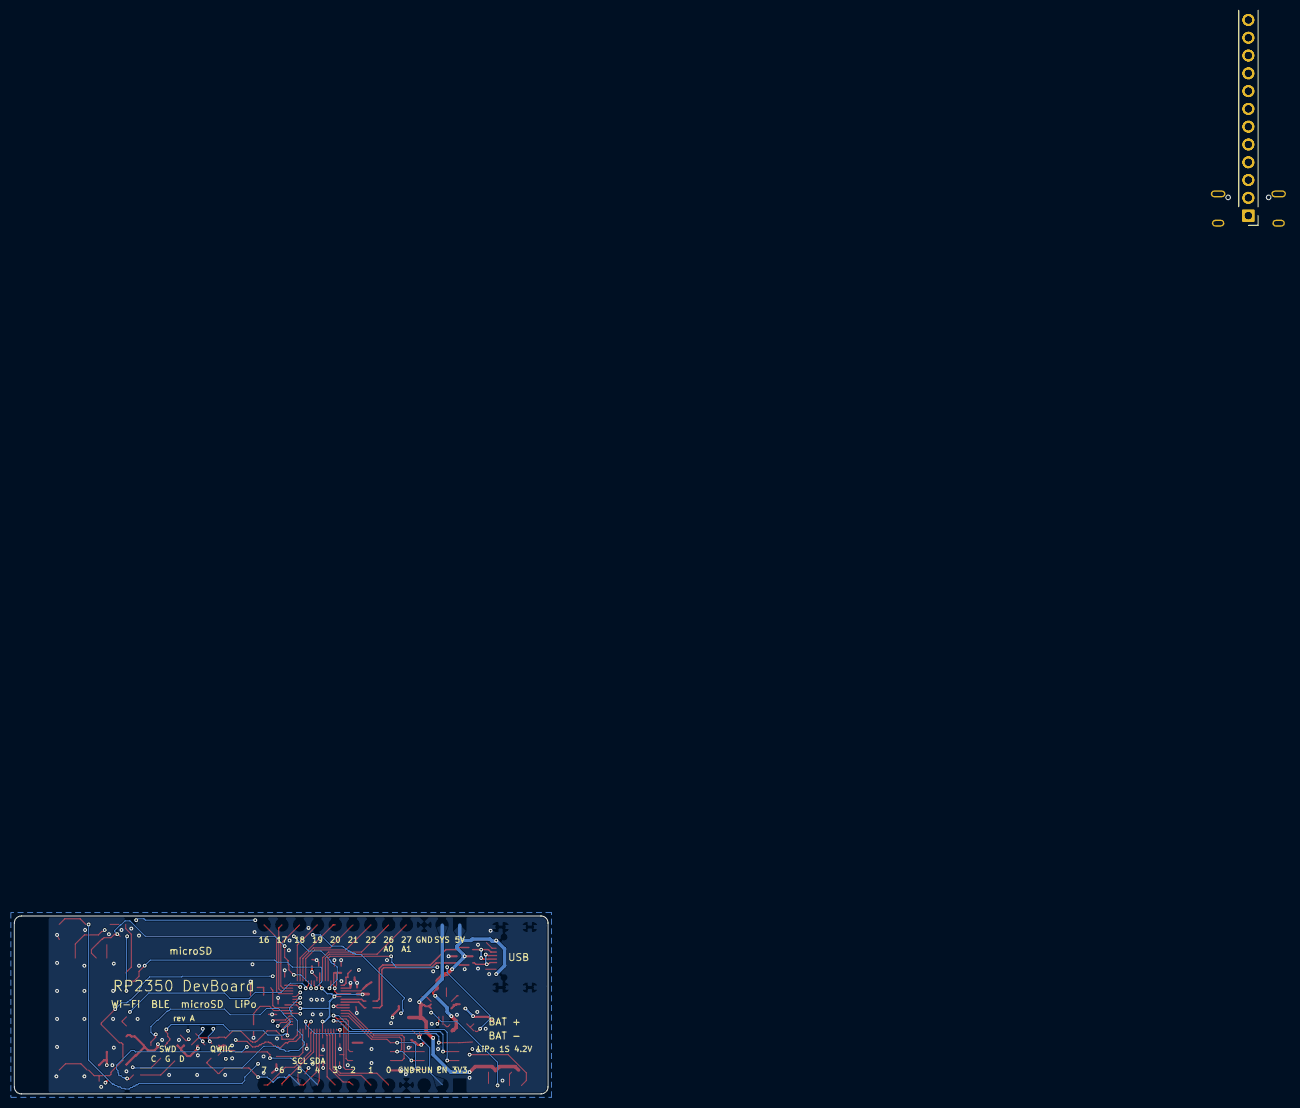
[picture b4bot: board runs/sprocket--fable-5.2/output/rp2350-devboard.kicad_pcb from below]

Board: 4 copper layers, 76.2 x 25.4 mm, 86 parts (2 on the bottom side), 72 nets.
